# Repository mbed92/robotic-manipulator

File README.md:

# robotic-manipulator

A small robotic manipulator project controlled by an Arduino Nano through a
PCA9685 servo driver. The repository contains Arduino firmware, the kinematic
model, angle-to-PWM mapping, calibration constants, and PCB files. This is my side project, 
and I had a lot of fun working on it. 

## Structure

- [`arduino/robot_arm/robot_arm.ino`](arduino/robot_arm/robot_arm.ino) - main firmware sketch.
- [`arduino/robot_arm/kinematics.h`](arduino/robot_arm/kinematics.h) / [`kinematics.cpp`](arduino/robot_arm/kinematics.cpp) - forward kinematics, Jacobian IK step generation, and angle-to-PWM conversion.
- [`arduino/robot_arm/robot_calibration.h`](arduino/robot_arm/robot_calibration.h) - servo channels, joint limits, HOME pose, and arm dimensions.
- [`arduino/robot_arm/pca9685_servo_driver.h`](arduino/robot_arm/pca9685_servo_driver.h) / [`pca9685_servo_driver.cpp`](arduino/robot_arm/pca9685_servo_driver.cpp) - PCA9685 driver wrapper.
- [`docs/bom.md`](docs/bom.md) - V1 prototype bill of materials.
- [`docs/lessons-learned.md`](docs/lessons-learned.md) - practical notes from calibration, IK debugging, and wiring.
- [`docs/TODO.md`](docs/TODO.md) - project task notes and planned improvements.
- [`pcb/`](pcb/) - KiCad PCB project.

## Hardware

The firmware assumes:

- an Arduino Nano microcontroller,
- a PCA9685 PWM driver on the I2C bus,
- six logical joints `J0-J5`, where `J0-J4` are part of the kinematic model
  and `J5` is the gripper.

The mechanical design and servo selection are based on material from
[Elektroweb](https://elektroweb.pl).

Joint indices map to PCA9685 channels defined in
`arduino/robot_arm/robot_calibration.h`.

## Kinematic Model

The manipulator is modeled as an arm with five kinematic joints:

- `J0` - base rotation around the vertical axis,
- `J1-J3` - pitch joints forming the planar arm chain,
- `J4` - local wrist/TCP rotation, independent of TCP position in the current model,
- `J5` - gripper, controlled outside the kinematic model.

TCP position is represented by the `TcpPose` structure:

- `reach_x_m` - reach in the arm plane, in meters,
- `reach_z_m` - TCP height, in meters,
- `yaw_rad` - base rotation, in radians.

Angle convention:

- all angles are in radians,
- `J1-J3 = 0` means that the arm segments point vertically upward,
- positive horizontal reach is computed with `sin(angle)`,
- height is computed with `cos(angle)`,
- `J0` controls the yaw of the whole arm,
- `J4` does not change the TCP position reported by forward kinematics.

Arm dimensions are stored in `JOINT_OFFSETS`:

- `L1` - vertical distance from base `J0` to shoulder `J1`,
- `L2-L4` - planar arm segment lengths,
- `L5` - offset from the last link to the TCP.

## Forward Kinematics

`forwardKinematics()` takes `J0-J4` joint angles and returns a `TcpPose`.
The computation accumulates consecutive pitch angles:

- `pitch_1 = J1`,
- `pitch_2 = J1 + J2`,
- `pitch_3 = J1 + J2 + J3`.

The TCP reach and height are then computed from link lengths `L2-L5`.
In the current model, `L4` and `L5` have the same direction as the final pitch
`J1 + J2 + J3`.

## Inverse Kinematics

The firmware uses an open-loop Jacobian IK trajectory generator based on the
commanded joint state:

- `computeJacobianIkStep()` is a pure numerical function. It computes one IK
  step from the current commanded joint angles, target, and configuration. It
  does not write PWM, wait, or access hardware.
- `moveToTargetJacobianIk()` in `robot_arm.ino` is the blocking hardware-facing
  trajectory generator. It calls the step function, checks limits, converts the
  next angles to PWM, writes the PCA9685 channels, waits until the next control
  period, and updates the commanded joint state.
- Before the planar DLS loop, the generator moves the explicitly commanded
  `J0`, `J3`, and `J4` axes toward their targets with the same fixed period and
  velocity limits. This gives the local Jacobian solve the intended `J3`
  geometry instead of starting from the vertical HOME singularity.

The IK task is:

- TCP reach,
- TCP height,
- base yaw,
- explicit `J3`,
- explicit `J4`.

Only the coupled planar subproblem `[reach, height, J3] <-> [J1, J2, J3]`
uses damped least squares. `J0` yaw and `J4` are handled as direct proportional
controllers with the same joint velocity and joint limit handling as the planar
joints. Task rows have explicit weights so meter and radian errors are scaled
before the DLS solve.

The solver limits joint velocity by computing a global `alpha` scale. If any
requested joint velocity exceeds its limit, the whole `q_dot` vector is scaled
by the smallest required ratio. For example, if a joint requests `3 rad/s` and
the limit is `2 rad/s`, the whole command is scaled by `2/3`. The current
default joint velocity limit is `0.5 rad/s` for each kinematic joint.

The default motion configuration uses a `20 ms` control period and allows up to
`500` iterations per target. With the default period this gives a maximum of
about `10 s` for one blocking target move before the target is reported as not
converged.

Joint limits also shrink the global step before failing the motion. A target is
reported as blocked only when the step scale is effectively exhausted while the
task error is still too large. The blocking motion loop also detects lack of
progress so the robot does not spend several seconds making tiny noisy motions
near an unreachable target.

Damped least squares does not remove physical singularities. Near a singular
configuration, some TCP directions are still not achievable by the mechanism.
DLS only prevents the numerical controller from asking for unbounded joint
velocities.

Because `J3` is an explicit task requirement and also part of the reach/height
kinematics, it restricts the reachable workspace. Some points that are
geometrically reachable with free `J3` may not be reachable when a specific
`J3` value is required.

Possible error statuses include:

- `OutOfReach` - the target did not converge within the configured iteration budget,
- `JointLimitViolation` - the current or computed command violates joint limits,
- `JointLimitBlocked` - joint limits prevent useful progress toward the target,
- `NoProgress` - the solver stopped reducing the normalized task error,
- `InvalidInput` - the input contains invalid values, such as `NaN` or infinity.

## Control Rules

The current firmware executes a fixed pick-and-place demo sequence during
startup:

1. `TARGET1` through `TARGET11` in `robot_arm.ino` define target `TcpPose`
   values, explicit `J3`, explicit `J4`, and gripper state.
2. `setup()` initializes the PCA9685, sends the arm to `ZERO`/HOME, and opens
   the gripper.
3. The robot moves through a blocking fixed-period Jacobian IK sequence: ready
   pose, pick-side yaw, descend, close gripper, lift, carry across a larger
   base rotation, descend, open gripper, retreat, and return to HOME.
4. The final HOME return is a normal Jacobian IK target, not a direct
   all-servo zero command.
5. Once the sequence is complete, `loop()` stays idle.

This is not closed-loop feedback from joint sensors. It is an open-loop
trajectory generator that assumes the commanded state is a reasonable estimate
of the servo state. Every new target and transition should still be tested
carefully on hardware.

## V1 Limitations

- No closed-loop feedback from joints.
- The Jacobian IK trajectory generator is blocking during the fixed demo
  sequence.
- IK solves TCP position and base yaw, not full 6D pose.
- `J3` and `J4` are explicit task inputs; `J3` constrains reachable TCP
  positions.
- Calibration is specific to this physical build and should not be copied
  blindly.
- Servo limits are conservative to avoid mechanical stops.

## Angle-To-PWM Mapping

`jointAnglesToPwmUs()` uses calibration values from `JOINT_CALIBRATIONS`.
For each joint, the calibration defines:

- PCA9685 channel,
- `pwm_min_us`, `pwm_zero_us`, `pwm_max_us`,
- `angle_min_rad`, `angle_zero_rad`, `angle_max_rad`.

The mapping is piecewise linear:

- from `angle_min_rad` to `angle_zero_rad`,
- from `angle_zero_rad` to `angle_max_rad`.

This also supports reversed servos, for example when `pwm_min_us` is greater
than `pwm_max_us`. The current `J3` calibration is one such case.

The `J5` gripper is controlled separately:

- `Open` uses `pwm_min_us`,
- `Closed` uses `pwm_max_us`.

## Lessons Learned

The main practical lessons are:

- mechanical zero is set by servo horn mounting first, then refined with
  `pwm_zero_us`,
- each joint needs its own zero, min, max, sign direction, and mechanical-stop
  check,
- IK commands should be sanity-checked by running FK on the resulting joint
  angles,
- Arduino logic power and servo power should be separated, with a common ground.

See [`docs/lessons-learned.md`](docs/lessons-learned.md) for the detailed notes.

## Startup Safety

Before testing on the manipulator, check:

- whether the target is within `JOINT_CALIBRATIONS` limits,
- whether `J3` and `J4` can cause a mechanical collision,
- whether the gripper PWM values are calibrated correctly,
- whether the open-loop IK motion can hit mechanical stops,
- whether the servo power supply is sufficient for multi-joint motion under load.

The safest test sequence is to compile first, then test without load, and only
then move with the final tool or object.

## Related Material

For broader teaching material on forward and inverse kinematics, see
[robotics-ai-classes](https://github.com/mbed92/robotics-ai-classes). That
repository contains ROS-based class exercises for FK and IK on a robotic
manipulator.

## Validation

Use Arduino CLI to validate firmware before testing on hardware:

```sh
arduino-cli compile --fqbn arduino:avr:nano arduino/robot_arm
```

For throwaway local builds, specify an explicit build path so generated
artifacts do not end up in the repository:

```sh
arduino-cli compile --fqbn arduino:avr:nano --build-path /tmp/robot_arm_build arduino/robot_arm
```

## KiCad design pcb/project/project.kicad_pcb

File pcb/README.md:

# PCB Wiring

## Connections

- Laptop USB -> Arduino USB
- Arduino +5V -> PCA9685 VCC/VDD
- Arduino GND -> PCA9685 GND/VSS
- Arduino SDA (pin A4) -> PCA9685 SDA
- Arduino SCL (pin A5) -> PCA9685 SCL
- PSU +5V -> PCA9685 V+
- PSU GND -> PCA9685 GND
- SERVO1..6 PWM -> PCA9685 CH1..6 PWM
- SERVO1..6 5V -> PCA9685 CH1..6 5V
- SERVO1..6 GND -> PCA9685 CH1..6 GND

## Important Notes

- Arduino does NOT power the servos.
- Servos are powered directly from PSU.
- All grounds must be connected together.
- PCA9685 generates hardware PWM signals.

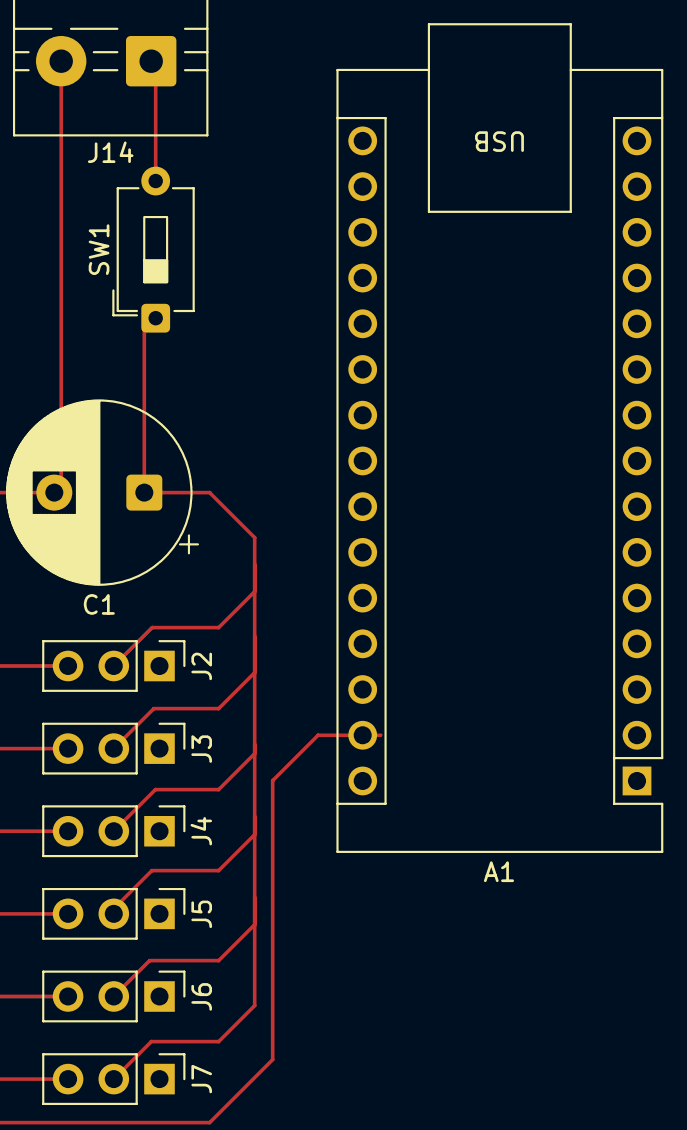
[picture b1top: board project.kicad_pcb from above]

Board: 2 copper layers, 10 parts (0 on the bottom side), 3 nets.

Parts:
A1: Arduino_Nano_v3.x; Arduino_Nano
C1: 1000uF / 25V; CP_Radial_D10.0mm_P5.00mm
J2: SERVO_BASE; PinHeader_1x03_P2.54mm_Vertical
J3: SERVO_SHOULDER; PinHeader_1x03_P2.54mm_Vertical
J4: SERVO_ELBOW; PinHeader_1x03_P2.54mm_Vertical
J5: SERVO_WRIST_PITCH; PinHeader_1x03_P2.54mm_Vertical
J6: SERVO_WRIST_ROT; PinHeader_1x03_P2.54mm_Vertical
J7: SERVO_GRIPPER; PinHeader_1x03_P2.54mm_Vertical
J14: POS-50-5-C2; TerminalBlock_MaiXu_MX126-5.0-02P_1x02_P5.00mm
SW1: SW_SPST; SW_DIP_SPSTx01_Slide_6.7x4.1mm_W7.62mm_P2.54mm_LowProfile

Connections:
/+5V_IN: J14.1, SW1.2 (B)
/+5V_SERVO: C1.1, J2.2, J3.2, J4.2, J5.2, J6.2, J7.2, SW1.1 (A)
/GND: A1.29 (GND), C1.2, J2.3, J3.3, J4.3, J5.3, J6.3, J7.3, J14.2

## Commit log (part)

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2026-05-26 feat: added wiring schema
2026-05-30 feat: add home position script and joint calibration configuration
2026-05-30 feat: add joint calibration and demo dance scripts for robot arm
2026-05-30 feat: implement PCA9685 servo driver and integrate with demo dance and go home scripts
2026-06-01 feat: update joint calibration parameters and rename home references to zero in demo scripts
2026-06-01 feat: refactor code style and improve consistency in joint calibration and servo driver files
2026-06-01 feat: remove ramp functionality and simplify servo control in PCA9685 driver
2026-06-01 feat: add robot calibration structures and update demo scripts to use new calibration header
2026-06-01 feat: implement kinematics module with forward and inverse kinematics functions, add kinematics debug sketch, and update related scripts
2026-06-01 feat: enhance inverse kinematics with new functions and improve kinematics validation in debug scripts
2026-06-01 feat: add simple Cartesian trajectory demo with trajectory computation and execution
2026-06-01 feat: refactor kinematics to use tool roll instead of yaw and update related trajectory calculations
2026-06-01 feat: add AGENTS.md for project overview, working style, decision framework, and engineering guidance
2026-06-01 feat: add Copilot instructions for build, test, and architecture overview
2026-06-01 TODO: validate with physical mapping
2026-06-02 Refactor kinematics and trajectory handling in robot arm code
    - Updated TcpPose structure to use yaw instead of pitch and yaw angles.
    - Renamed inverse kinematics functions to reflect changes in pose representation.
    - Modified trajectory computation to use updated inverse kinematics functions.
    - Improved comments for clarity on trajectory execution and TCP positioning.
    - Removed deprecated kinematics debug sketch to streamline the codebase.
    - Added home joint angles constants and functions for better initialization.
2026-06-02 feat: enhance inverse kinematics with TCP offset pitch and refactor trajectory handling
2026-06-02 refactor: update kinematics calculations and simplify TCP pose representation
2026-06-02 refactor: simplify inverse kinematics logic and remove unused function
2026-06-02 feat: enhance inverse kinematics with explicit J3 pitch handling and update calibration for joint 3
2026-06-08 refactor: remove demo dance scripts and related kinematics files
2026-06-08 feat: add kinematics status name function and update target command handling
2026-06-08 docs: update README and TODO with detailed project structure and external controller integration plan
2026-06-08 feat: implement fixed Cartesian target sequence with multiple target commands
2026-06-08 docs: enhance README with lessons learned and add project image
2026-06-08 docs: update control rules in README to reflect fixed Cartesian target sequence during startup
2026-06-08 refactor: remove setServoUsImmediate method and update usage in setServoUs
2026-06-08 docs: add MG996R Tower Pro datasheet PDF to assets
2026-06-08 docs: add detailed lessons learned section to improve calibration and kinematics understanding
2026-06-08 docs: add V1 limitations section to README for clarity on current constraints
2026-06-08 docs: add bill of materials and TODO sections to enhance project documentation
2026-06-08 docs: add source attribution for mechanical design and servo selection
2026-06-08 docs: update references to target commands in TODO and AGENTS documentation
2026-06-08 docs: update file references in README structure for clarity
